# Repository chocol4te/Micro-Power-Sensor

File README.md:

# Micro-Power-Sensor
A simple, small current and voltage sensor outputting analog and serial readings.

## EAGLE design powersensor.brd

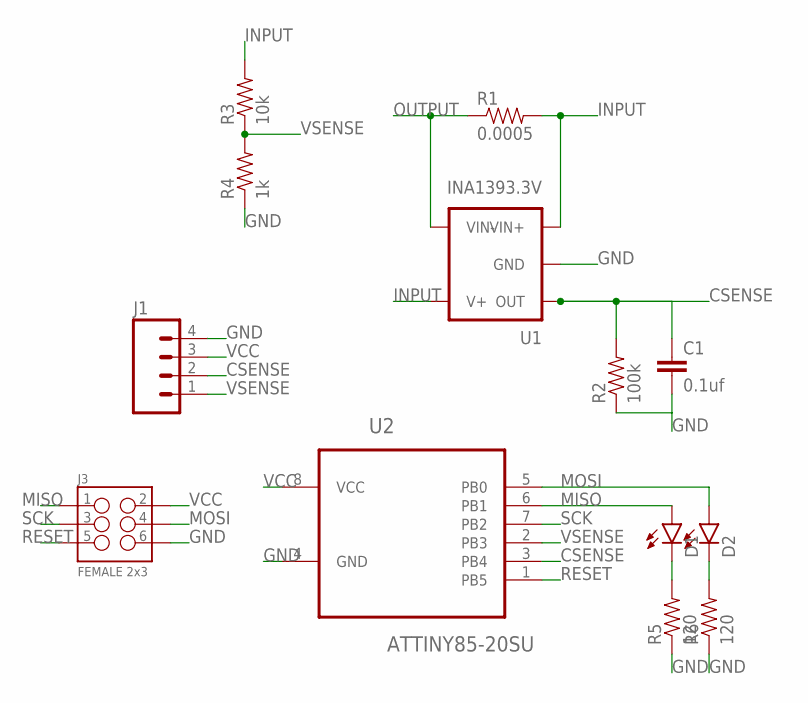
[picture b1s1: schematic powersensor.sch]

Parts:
C1: 0.1uf; 0603-CAP
D1, D2: LED0603; LED-0603
J1: M04PTH; 1X04
J3: FEMALE 2x3; 2X3
R1: 0.0005; R2512
R2: 100k; 0603-RES
R3: 10k; 0603-RES
R4: 1k; 0603-RES
R5, R6: 120; 0603-RES
U1: INA1393.3V; SOT23-5
U2: ATTINY85-20SU; SOIC127P798X216-8N

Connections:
CSENSE: C1.1, J1.2, R2.2, U1.1 (OUT), U2.3 (PB4)
GND: C1.2, J1.4, J3.6, R2.1, R4.1, R5.1, R6.1, U1.2 (GND), U2.4 (GND)
INPUT: R1.2, R3.2, U1.3 (VIN+), U1.5 (V+)
MISO: D1.A, J3.1, U2.6 (PB1)
MOSI: D2.A, J3.4, U2.5 (PB0)
unnamed: D1.C, R5.2
unnamed: D2.C, R6.2
OUTPUT: R1.1, U1.4 (VIN-)
RESET: J3.5, U2.1 (PB5)
SCK: J3.3, U2.7 (PB2)
VCC: J1.3, J3.2, U2.8 (VCC)
VSENSE: J1.1, R3.1, R4.2, U2.2 (PB3)

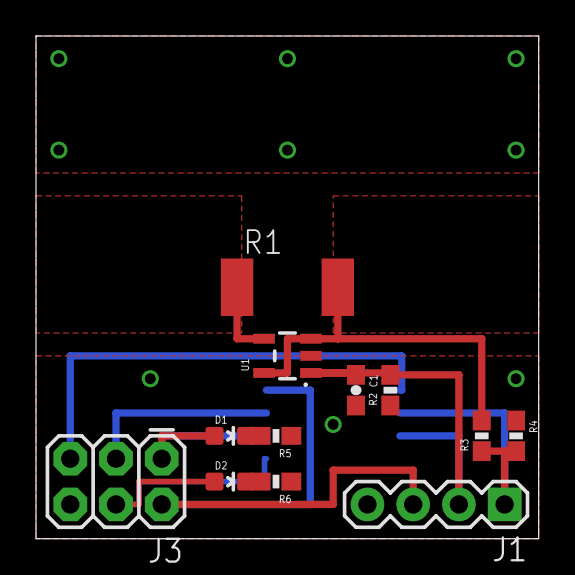
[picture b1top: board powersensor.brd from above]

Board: 2 copper layers, 27.9 x 27.9 mm, 13 parts (1 on the bottom side), 12 nets.

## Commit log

2016-02-22 Initial commit of Eagle files

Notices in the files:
parts and their libraries:
SparkFun-Passives: Licensing: Creative Commons ShareAlike 4.0 International - https://creativecommons.org/licenses/by-sa/4.0
